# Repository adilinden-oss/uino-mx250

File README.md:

## \*uino-mx250

The \*uino-mx250 was designed for my son Mathew. As a mostly though-hole design, it should be easy to assemble even for a beginner.  The only surface mount component is the micro USB connector. Personally I much prefer micro USB over the full sized or mini connector. Unfortunately I was unable to find a through-hole micro USB.  Having the one surface mounted component was a compromise I was willing to take.

The board uses the PIC32MX250F128B which is available in a 28 pin through-hole package and includes an on-board USB peripheral.  The PIC32MX250F128B is supported by [chipKIT Core](http://chipkit.net/wiki/index.php?title=ChipKIT_core) for the [Arduino](https://www.arduino.cc/) development environment.  Select the chipKIT DP32.

### Important Note

PCB have been ordered from SeeedStudio FusionPCB service. There is no working sample yet.

### Licensing

This work is licensed under a Creative Commons Attribution-ShareAlike 3.0 Unported License, CC BY-SA.

You are free to copy, distribute and transmit the work. You must attribute the work in the manner specified by the author or licensor (but not in any way that suggests that they endorse you or your use of the work). you alter, transform, or build upon this work, you may distribute the resulting work only under the same or similar license to this one.  

Please refer to [http://creativecommons.org/licenses/by-sa/3.0/] for the license.

### Credit

The \*uino-mx250 is derived from previous work done by:

- The [chipKIT DP32](https://reference.digilentinc.com/chipkit_dp32/refmanual)
- The [HelvePic32](http://www.mathias-wilhelm.de/arduino/embedded-boards/helvepic32)

### Details

Aside from teaching my son how to solder, the motivation for the \*uino-mx250 was to create a through-hole chipKIT board that can make use of existing shields.  The \*uino-mx250 is intended to operate at 3.3V as this is the operating voltage of the PIC32MX250F128B.

Mostly due to the use of the USB peripheral, the PIC32MX250F128B has less available I/O than the ATmega328P. Some compromises and choices were necessary to map the PIC32MX250F128B I/O to the shield pins.  In particular analog pins A1, A2, A3, A4 and A5 are directly connected to digital pins D12, D10, D11, D9 and D8.  This is important to remember!

PIC32MX250F128B I/O is mapped to shield pins to preserve the special functions of the digital pins.  Thanks to PIC32 mappable peripheral pins I2C, SPI, serial and PWM functions are were they should be. Still, some compromises were necessary, either D3 or D11 can use OC2 for PWM, but not both at the same time.

### Pin Mapping

```
        PIC32MX250F128B                                     Peripheral
D0      SOSCO/RPA4/T1CK/CTED9/PMA1/RA4                      RX1         RxD
D1      TDI/RPB7/CTED3/PMD5/INT0/RB7                        TX1         TxD
D2      PGED3/RPB5/PMD7/RB5
D3      TCK/RPB8/SCL1/CTED10/PMD4/RB8                       OC2         PWM
D4      TDO/RPB9/SDA1/CTED4/PMD3/RB9
D5      SOSCI/RPB4/RB4                                      OC1         PWM
D6      AN11/RPB13/CTPLS/PMRD/RB13                          OC4/5       PWM
D7      AN9/C3INA/RPB15/SCK2/CTED6/PMCS1/RB15

D8  A5  AN5/C1INA/C2INC/RTCC/RPB3/SCL2/RB3 
D9  A4  AN4/C1INB/C2IND/RPB2/SDA2/CTED13/RB2                OC4/5       PWM
D10 A2  PGED1/AN2/C1IND/C2INB/C3IND/RPB0/RB0                OC3         PWM
D11 A3  PGEC1/AN3/C1INC/C2INA/RPB1/CTED12/RB1               OC2 DO1     PWM MOSI
D12 A1  PGEC3/VREF-/CVREF-/AN1/RPA1/CTED2/PMD6/RA1          DI          MISO
D13     CVREFOUT/AN10/C3INB/RPB14/SCK1/CTED5/PMWR/RB14      SCK1        SCK

A0      PGED3/VREF+/CVREF+/AN0/C3INC/RPA0/CTED1/PMD7/RA0
A1 D12  PGEC3/VREF-/CVREF-/AN1/RPA1/CTED2/PMD6/RA1
A2 D10  PGED1/AN2/C1IND/C2INB/C3IND/RPB0/RB0
A3 D11  PGEC1/AN3/C1INC/C2INA/RPB1/CTED12/RB1
A4 D9   AN4/C1INB/C2IND/RPB2/SDA2/CTED13/RB2                SDA2        SDA
A5 D8   AN5/C1INA/C2INC/RTCC/RPB3/SCL2/RB3                  SCL2        SCL

```

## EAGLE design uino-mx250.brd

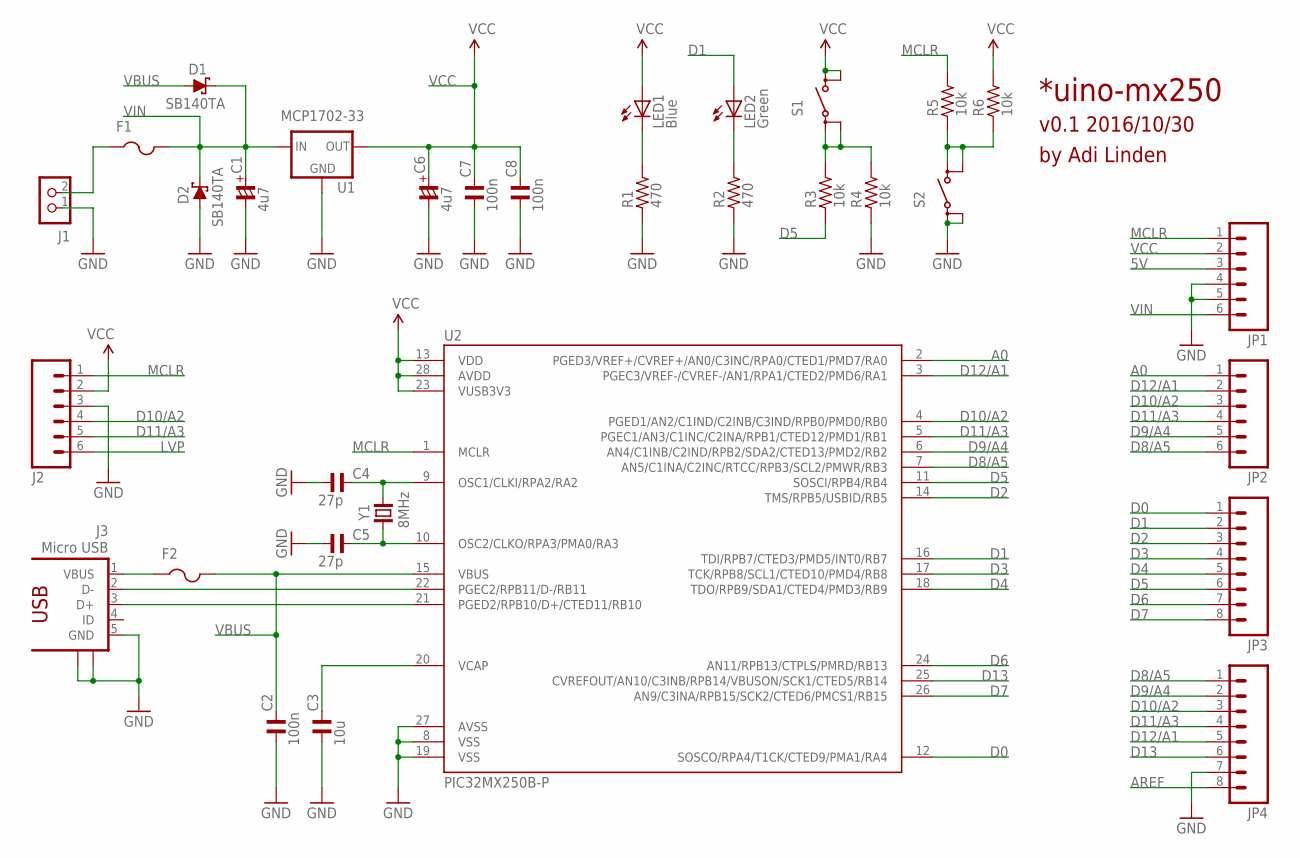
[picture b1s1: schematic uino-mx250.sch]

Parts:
C1, C6: 4u7; CTT-025-040
C2, C7, C8: 100n; C025-040X018
C3: 10u; C025-040X018
C4, C5: 27p; C025-040X018
D1, D2: SB140TA; DO35-7
F1, F2: FUSE_PTC-TH; PTC
J1: CON_TERMINAL_BLOCK_02-5MM; TERMINAL_BLOCK_2P_5
J2: M06LOCK; 1X06_LOCK
J3: Micro USB; ZX62D-AB-5P8
JP1, JP2: M06SIP; 1X06
JP3, JP4: M081X08; 1X08
LED1: Blue; LED3MM
LED2: Green; LED3MM
R1, R2: 470; 0207/7
R3, R4, R5, R6: 10k; 0207/7
S1, S2: TL1100X
U1: MCP1702-33; TO-92
U2: PIC32MX250B-P; DIL28-3
Y1: 8MHz; HC49/S

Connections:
5V: JP1.3
A0: JP2.1, U2.2 (PGED3/VREF+/CVREF+/AN0/C3INC/RPA0/CTED1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)
AREF: JP4.8
D0: JP3.1, U2.12 (SOSCO/RPA4/T1CK/CTED9/PMA1/RA4)
D1: JP3.2, LED2.A, U2.16 (TDI/RPB7/CTED3/PMD5/INT0/RB7)
D2: JP3.3, U2.14 (TMS/RPB5/USBID/RB5)
D3: JP3.4, U2.17 (TCK/RPB8/SCL1/CTED10/PMD4/RB8)
D4: JP3.5, U2.18 (TDO/RPB9/SDA1/CTED4/PMD3/RB9)
D5: JP3.6, R3.1, U2.11 (SOSCI/RPB4/RB4)
D6: JP3.7, U2.24 (AN11/RPB13/CTPLS/PMRD/RB13)
D7: JP3.8, U2.26 (AN9/C3INA/RPB15/SCK2/CTED6/PMCS1/RB15)
D8/A5: JP2.6, JP4.1, U2.7 (AN5/C1INA/C2INC/RTCC/RPB3/SCL2/PMWR/RB3)
D9/A4: JP2.5, JP4.2, U2.6 (AN4/C1INB/C2IND/RPB2/SDA2/CTED13/PMD2/R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)
D10/A2: J2.4, JP2.3, JP4.3, U2.4 (PGED1/AN2/C1IND/C2INB/C3IND/RPB0/PMD0/R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)
D11/A3: J2.5, JP2.4, JP4.4, U2.5 (PGEC1/AN3/C1INC/C2INA/RPB1/CTED12/PMD1/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)
D12/A1: JP2.2, JP4.5, U2.3 (PGEC3/VREF-/CVREF-/AN1/RPA1/CTED2/PMD6/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)
D13: JP4.6, U2.25 (CVREFOUT/AN10/C3INB/RPB14/VBUSON/SCK1/C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)
GND: C1.-, C2.1, C3.1, C4.1, C5.1, C6.-, C7.1, C8.1, D2.A, J1.1, J2.3, J3.5 (GND), J3.S1, J3.S2, JP1.4, JP1.5, JP4.7, R1.1, R2.1, R4.1, S2.1, S2.2 (P1), U1.1 (GND), U2.8 (VSS), U2.19 (VSS), U2.27 (AVSS)
LVP: J2.6
MCLR: J2.1, JP1.1, R5.2, U2.1 (MCLR)
unnamed: F1.P$1 (1), J1.2
unnamed: F2.P$1 (1), J3.1 (VBUS)
unnamed: LED1.K (C), R1.2
unnamed: LED2.K (C), R2.2
unnamed: R3.2, R4.2, S1.1, S1.2 (P1)
unnamed: R5.1, R6.1, S2.3 (S), S2.4 (S1)
unnamed: C3.2, U2.20 (VCAP)
unnamed: J3.2 (D-), U2.22 (PGEC2/RPB11/D-/RB11)
unnamed: J3.3 (D+), U2.21 (PGED2/RPB10/D+/CTED11/RB10)
unnamed: C4.2, U2.9 (OSC1/CLKI/RPA2/RA2), Y1.2
unnamed: C5.2, U2.10 (OSC2/CLKO/RPA3/PMA0/RA3), Y1.1
VBUS: C2.2, D1.A, F2.P$2 (2), U2.15 (VBUS)
VCC: C6.+, C7.2, C8.2, J2.2, JP1.2, LED1.A, R6.2, S1.3 (S), S1.4 (S1), U1.3 (OUT), U2.13 (VDD), U2.23 (VUSB3V3), U2.28 (AVDD)
VIN: C1.+, D1.C, D2.C, F1.P$2 (2), JP1.6, U1.2 (IN)

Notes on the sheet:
*uino-mx250
v0.1 2016/10/30
by Adi Linden

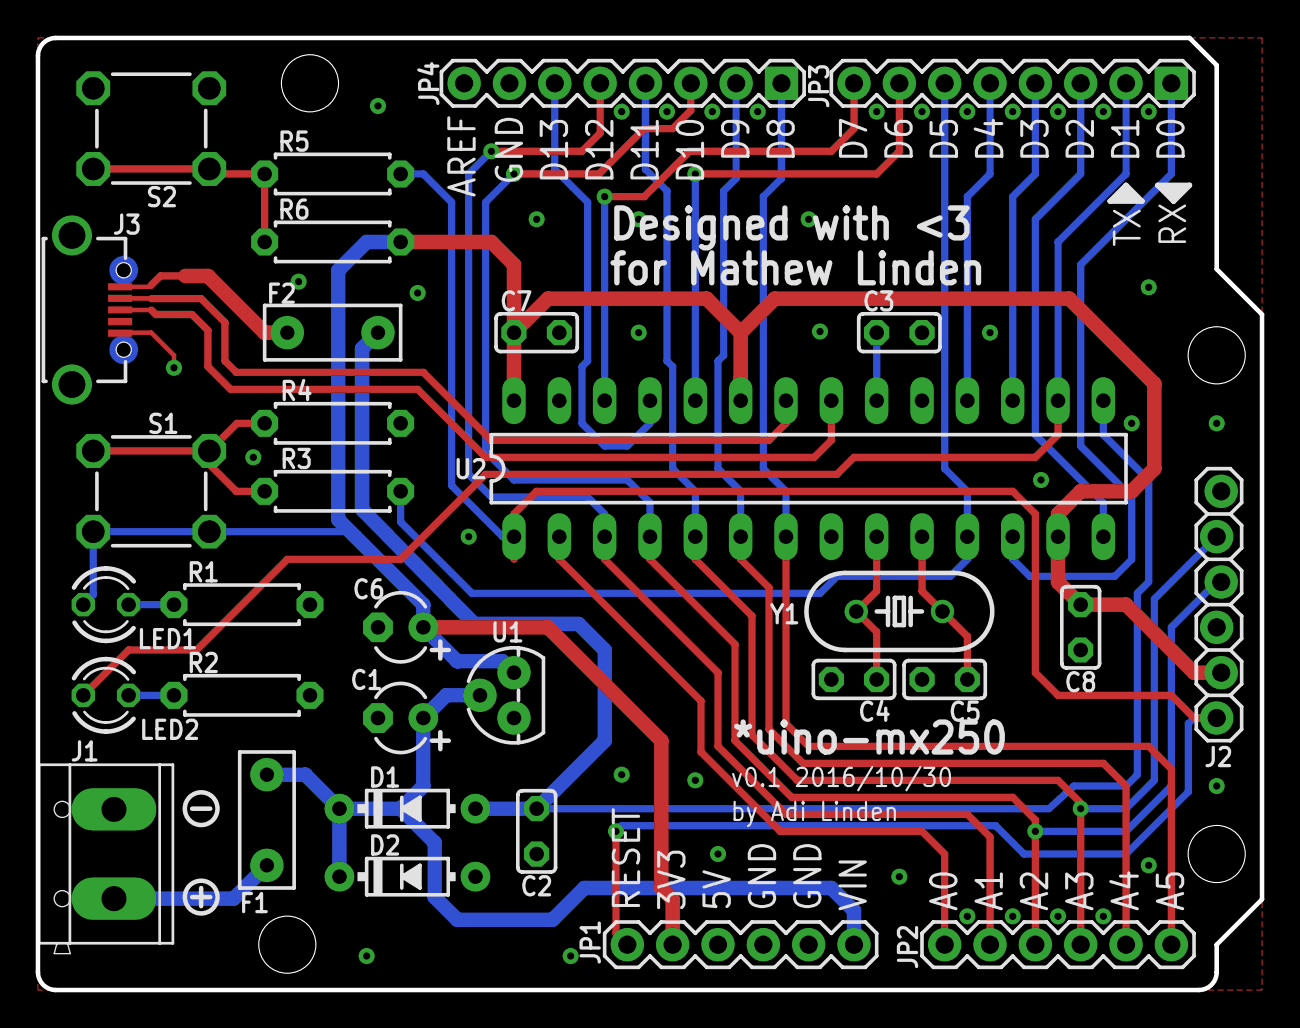
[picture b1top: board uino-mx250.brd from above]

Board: 2 copper layers, 68.6 x 53.3 mm, 32 parts (0 on the bottom side), 31 nets.

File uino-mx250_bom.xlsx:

Parts | Qty | Value | Manufacturer Part Number | DigiKey Part Number | Package | Description
C1, C6 | 2 | 4u7 | TAP475M010SCS | 478-8841-ND | 2.5mm | 4.7µF ±20% Conformal Coated Tantalum Capacitors 10V Radial 8 Ohm
C2, C7, C8 | 3 | 100n | K104Z15Y5VF5TL2 | BC1160CT-ND | 2.5mm | 0.10µF -20%, +80% 50V Ceramic Capacitor Y5V (F) Radial
C3 | 1 | 10u | FK16X7R1C106K | 445-8348-ND | C025-040X018 | 10µF ±10% 16V Ceramic Capacitor X7R Radial
C4, C5 | 2 | 22p | K220J15C0GF5TL2 | BC1005CT-ND | C025-040X018 | 22pF ±5% 50V Ceramic Capacitor C0G, NP0 Radial
D1, D2 | 2 | 1A | SB140TA | 1655-1514-1-ND | DO-41 | Diode Schottky 40V 1A Through Hole DO-41
F1, F2 | 2 | 400mA | 0ZRC0040FF1E | 507-1335-ND | 5mm | PTC Resettable Fuse 90V 400mA Ih Through Hole Radial, Disc
J1 | 1 | CON_TERMINAL_BLOCK_02-5MM | OSTTC022162 | ED2609-ND | 5mm | 2 Position Wire to Board Terminal Block Horizontal with Board 0.200" (5.08mm) T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
J2 | 1 | Header 1x6 | M20-9990645 | 952-2269-ND | 1X06 | 6 Positions Header, Unshrouded, Breakaway Connector 0.100" (2.54mm) Through Hol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
J3 | 1 | Micro USB | 475890001 | WM17143CT-ND | ZX62D-AB-5P8 | USB - micro AB Receptacle Connector 5 Position Surface Mount, Right Angle, Hori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
JP1, JP2 | 2 | Header 1x6 | PPTC061LFBN-RC | S7004-ND | 1X06 | 6 Position Header Connector 0.100" (2.54mm) Through Hole Tin
JP3, JP4 | 2 | Header 1x8 | PPTC081LFBN-RC | S7006-ND | 1X08 | 8 Position Header Connector 0.100" (2.54mm) Through Hole Tin
LED1 | 1 | Red | 151033RS03000 | 732-5013-ND | LED3MM | Red 621nm LED Indication - Discrete 2V Radial
LED2 | 1 | Green | HLMP1540 | 1080-1046-ND | LED3MM | Green LED Indication - Discrete 2.2V Radial
R1, R2 | 2 | 470 | CF14JT470R | CF14JT470RCT-ND | 0207/7 | RES 470 OHM 1/4W 5% CARBON FILM
R3, R4, R5, R6 | 4 | 10k | CF14JT10K0 | CF14JT10K0CT-ND | 0207/7 | RES 10K OHM 1/4W 5% CARBON FILM
S1, S2 | 2 | Tactile Switch | 1825910-6 | 450-1650-ND | TL1100X | Tactile Switch SPST-NO Top Actuated Through Hole
U1 | 1 | MCP1702-33 | MCP1702-3302E/TO | MCP1702-3302E/TO-ND | TO-92 | Linear Voltage Regulator IC Positive Fixed 1 Output 3.3V 250mA TO-92-3
U2 | 1 | PIC32MX250B-I/SP | PIC32MX270F256B-I/SP | PIC32MX270F256B-I/SP-ND | DIL28-3 | MIPS32® M4K™ PIC® 32MX Microcontroller IC 32-Bit 40MHz 256KB (256K x 8) FLASH 2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
Y1 | 1 | 8MHz | ABL-8.000MHZ-B2 | 535-9062-ND | HC49/S | 8MHz ±20ppm Crystal 18pF 80 Ohm -20°C ~ 70°C Through Hole HC49/US

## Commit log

2016-10-29 Added templates to build uino-mx250.
2016-10-30 First working cut.
2016-10-30 Adjusted power input layout.
2016-10-31 Created/updated Eagle project. Added .gitignore.
2016-10-31 Some minor final changes.
2016-10-31 Ran cam to generate gerber.
2016-11-04 Added values. Added png files.
2016-11-04 Added README.md.
2016-11-04 Fixed typos.
2016-11-14 Added BOM.
2016-11-14 Created gerber for SeeedStudio FusionPCB order.
2019-02-22 Fixed formatting.

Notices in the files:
parts and their libraries:
SparkFun-Connectors: Licensing: Creative Commons ShareAlike 4.0 International - https://creativecommons.org/licenses/by-sa/4.0
rc-master: Copyright (C) 2007-2008, Bob Starr
